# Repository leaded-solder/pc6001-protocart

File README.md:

# PC-6001 Pico Cartridge
Raspberry Pi Pico based cartridge

# Version History
## v1.2
Refined version of v1.1
 - Add pull-up to data buffer IN/out to make sure it works properly during startup (paranoid)
 - Make address lines always IN using a +3.3v pull-up
 - Bypass caps for 74lvc245 to improve performance (paranoid)
 - Z80 WAIT pin wired to GPIO 27

## v1.1 (released)
Adds buffers for address/data multiplexing purposes

## v1.0 (released)
Initial version, unbuffered

# Open source stuff used
 * [Pablo Oyarzo poka-yoke library](https://github.com/PabloOyarzo/poka-yoke_rxtx)

# Special Thanks
 * alank2 on the Vintage Computer Festival forum, for measuring his Canyon Climber cartridge
 * thweasel on the FujiNet discord for helping check my design

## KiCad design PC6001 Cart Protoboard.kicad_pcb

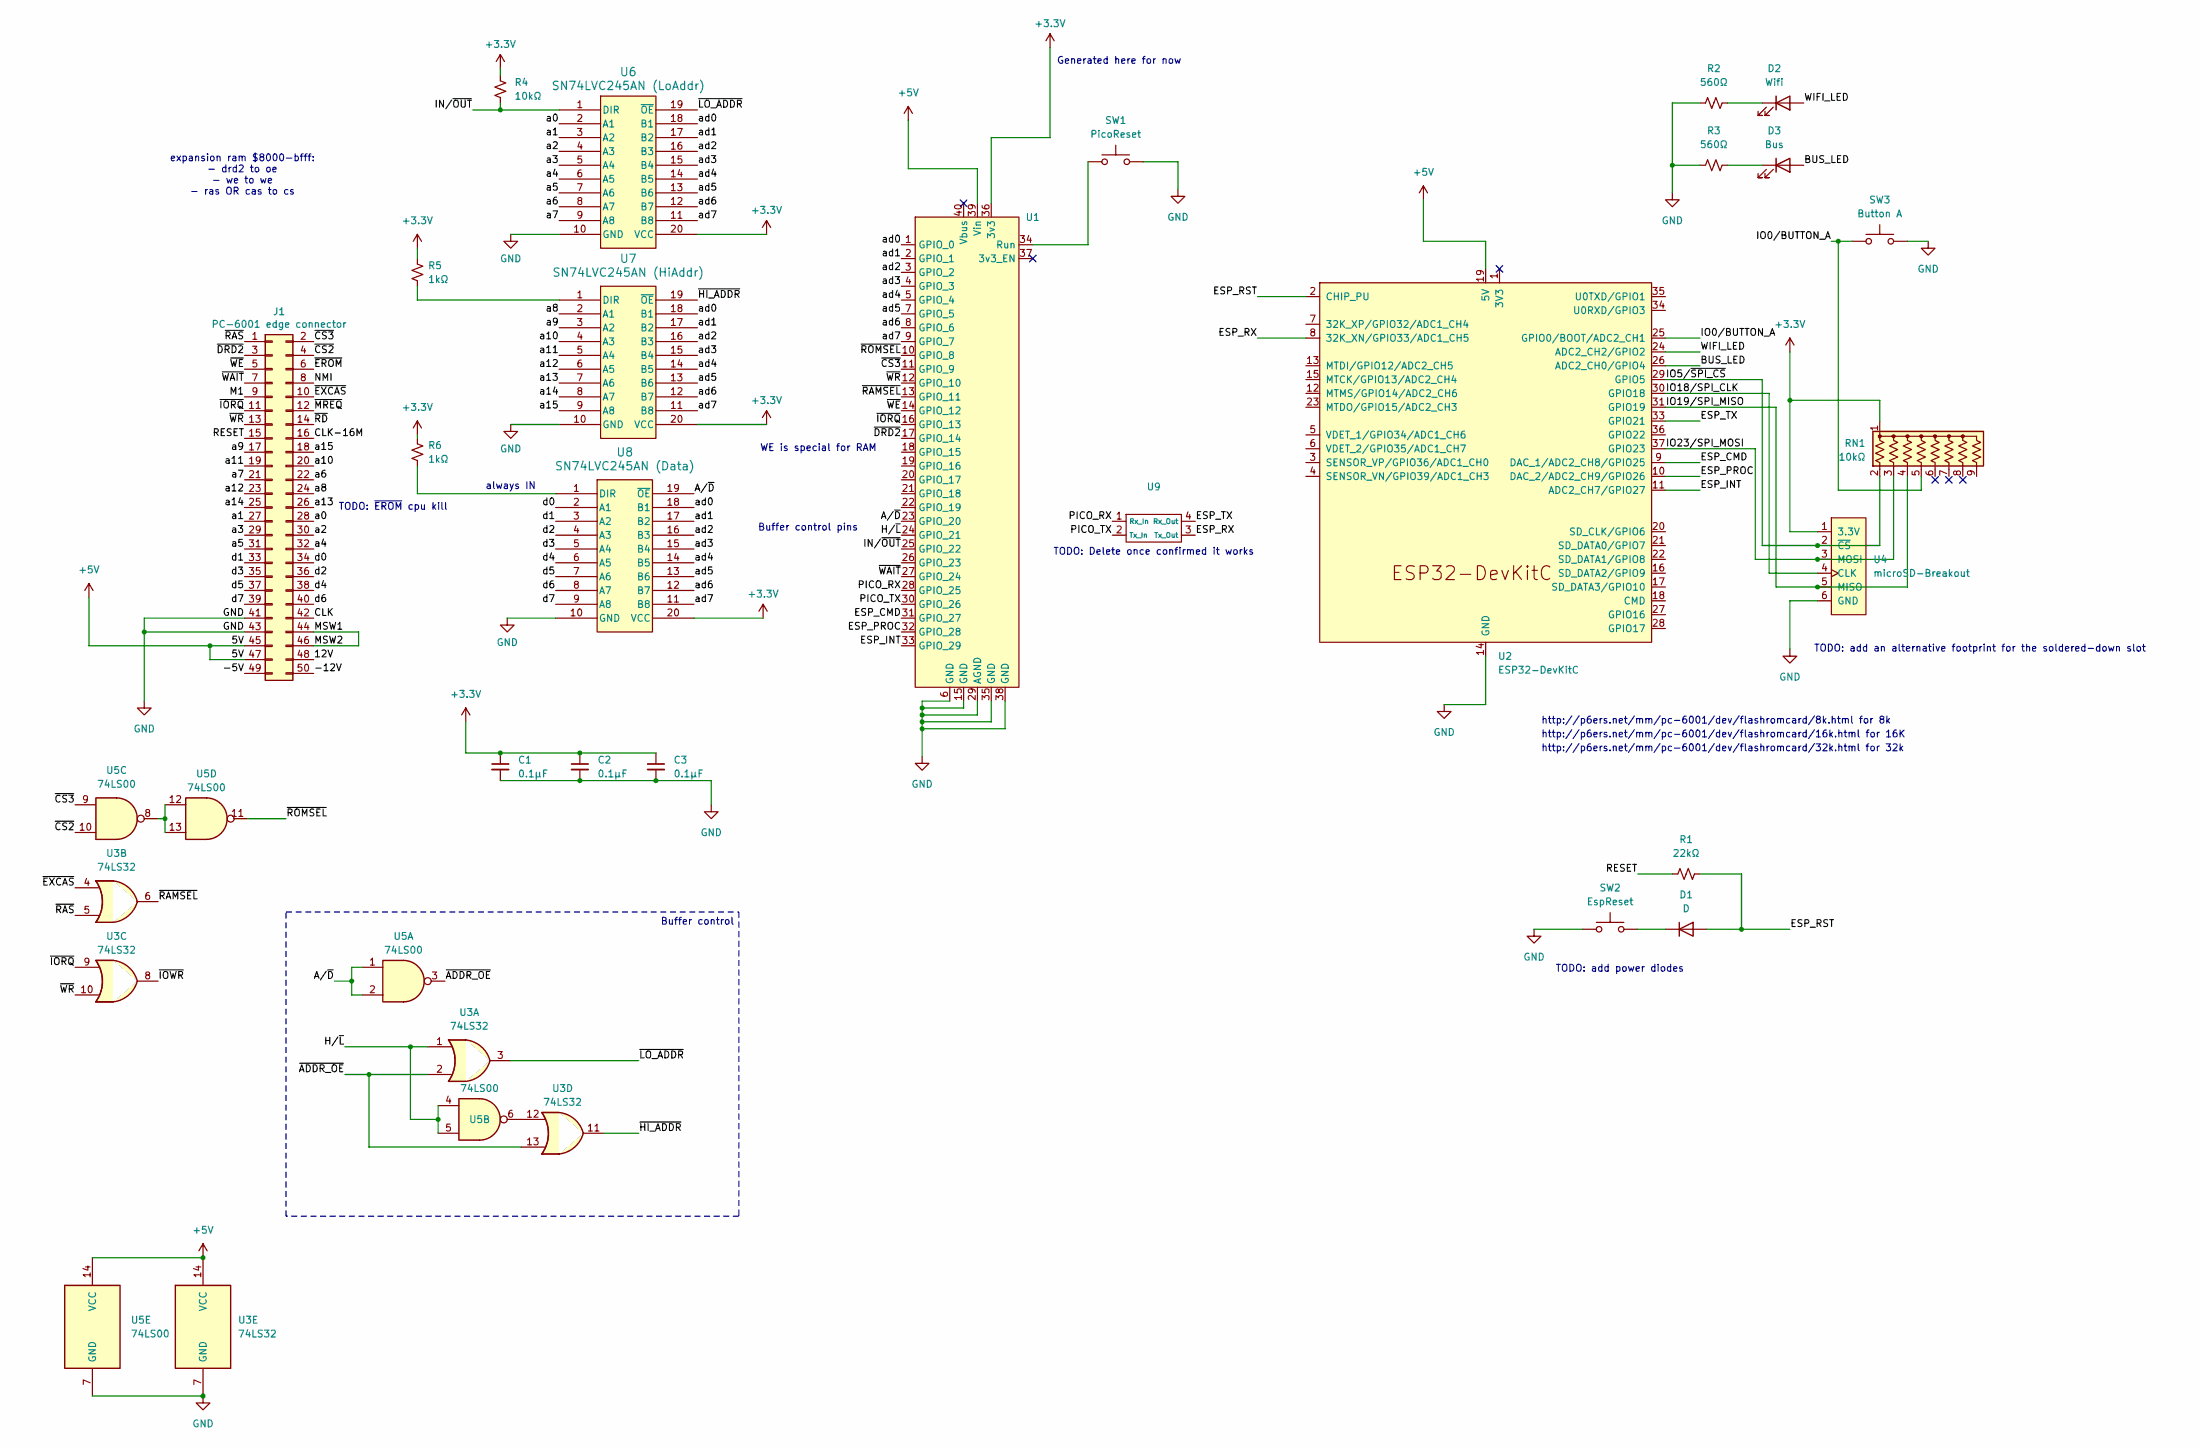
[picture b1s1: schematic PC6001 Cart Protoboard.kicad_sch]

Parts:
C1, C2, C3: 0.1µF; C_Disc_D5.0mm_W2.5mm_P2.50mm
D1: D; D_DO-35_SOD27_P7.62mm_Horizontal
D2: Wifi; LED_D3.0mm
D3: Bus; LED_D3.0mm
J1: PC-6001 edge connector; PC6001 Cartridge Connector
R1: 22kΩ; R_Axial_DIN0207_L6.3mm_D2.5mm_P10.16mm_Horizontal
R2, R3: 560Ω; R_Axial_DIN0207_L6.3mm_D2.5mm_P10.16mm_Horizontal
R4: 10kΩ; R_Axial_DIN0207_L6.3mm_D2.5mm_P10.16mm_Horizontal
R5, R6: 1kΩ; R_Axial_DIN0207_L6.3mm_D2.5mm_P10.16mm_Horizontal
RN1: 10kΩ; R_Array_SIP9
SW1: PicoReset; SW_PUSH_6mm
SW2: EspReset; SW_PUSH_6mm
SW3: Button A; SW_PUSH_6mm
U1: UltimatePico
U2: ESP32-DevKitC
U3: 74LS32
U4: microSD-Breakout; microSD_AliExpress
U5: 74LS00; DIP-14_W7.62mm_Socket_LongPads
U6: SN74LVC245AN (LoAddr); DIP-20_W7.62mm_Socket_LongPads
U7: SN74LVC245AN (HiAddr); DIP-20_W7.62mm_Socket_LongPads
U8: SN74LVC245AN (Data); DIP-20_W7.62mm_Socket_LongPads
U9: poka-yoke_rxtx

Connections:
+3.3V: C1.1, C2.1, C3.1, R4.1, R5.1, R6.1, RN1.1 (common), U1.36 (3v3), U4.1 (3.3V), U6.20 (VCC), U7.20 (VCC), U8.20 (VCC)
+5V: J1.45, J1.47, U1.39 (Vin), U2.19 (5V), U3.14 (VCC), U5.14 (VCC)
/12V: J1.48
/-5V: J1.49
/-12V: J1.50
/A/~D: U1.23 (GPIO_20), U5.1, U5.2, U8.19 (~OE)
/BUS_LED: D3.2 (A), U2.26 (ADC2_CH0/GPIO4)
/CLK: J1.42
/CLK-16M: J1.16
/ESP_CMD: U1.31 (GPIO_27), U2.9 (DAC_1/ADC2_CH8/GPIO25)
/ESP_INT: U1.33 (GPIO_29), U2.11 (ADC2_CH7/GPIO27)
/ESP_PROC: U1.32 (GPIO_28), U2.10 (DAC_2/ADC2_CH9/GPIO26)
/ESP_RST: D1.2 (A), R1.2, U2.2 (CHIP_PU)
/ESP_RX: U2.8 (32K_XN/GPIO33/ADC1_CH5), U9.3 (Tx_Out)
/ESP_TX: U2.33 (GPIO21), U9.4 (Rx_Out)
/H/~L: U1.24 (GPIO_21), U3.1, U5.4, U5.5
/IN/~OUT: R4.2, U1.25 (GPIO_22), U6.1 (DIR)
/IO0/BUTTON_A: RN1.5 (R4), SW3.1, U2.25 (GPIO0/BOOT/ADC2_CH1)
/IO5/~SPI_CS: RN1.2 (R1), U2.29 (GPIO5), U4.2 (~CS)
/IO18/SPI_CLK: U2.30 (GPIO18), U4.4 (CLK)
/IO19/SPI_MISO: RN1.4 (R3), U2.31 (GPIO19), U4.5 (MISO)
/IO23/SPI_MOSI: RN1.3 (R2), U2.37 (GPIO23), U4.3 (MOSI)
/M1: J1.9
/MSW1: J1.44, J1.46
/NMI: J1.8
/PICO_RX: U1.28 (GPIO_25), U9.1 (Rx_In)
/PICO_TX: U1.30 (GPIO_26), U9.2 (Tx_In)
/RESET: J1.15, R1.1
/WIFI_LED: D2.2 (A), U2.24 (ADC2_CH2/GPIO2)
/a0: J1.28, U6.2 (A1)
/a1: J1.27, U6.3 (A2)
/a2: J1.30, U6.4 (A3)
/a3: J1.29, U6.5 (A4)
/a4: J1.32, U6.6 (A5)
/a5: J1.31, U6.7 (A6)
/a6: J1.22, U6.8 (A7)
/a7: J1.21, U6.9 (A8)
/a8: J1.24, U7.2 (A1)
/a9: J1.17, U7.3 (A2)
/a10: J1.20, U7.4 (A3)
/a11: J1.19, U7.5 (A4)
/a12: J1.23, U7.6 (A5)
/a13: J1.26, U7.7 (A6)
/a14: J1.25, U7.8 (A7)
/a15: J1.18, U7.9 (A8)
/ad0: U1.1 (GPIO_0), U6.18 (B1), U7.18 (B1), U8.18 (B1)
/ad1: U1.2 (GPIO_1), U6.17 (B2), U7.17 (B2), U8.17 (B2)
/ad2: U1.3 (GPIO_2), U6.16 (B3), U7.16 (B3), U8.16 (B3)
/ad3: U1.4 (GPIO_3), U6.15 (B4), U7.15 (B4), U8.15 (B4)
/ad4: U1.5 (GPIO_4), U6.14 (B5), U7.14 (B5), U8.14 (B5)
/ad5: U1.7 (GPIO_5), U6.13 (B6), U7.13 (B6), U8.13 (B6)
/ad6: U1.8 (GPIO_6), U6.12 (B7), U7.12 (B7), U8.12 (B7)
/ad7: U1.9 (GPIO_7), U6.11 (B8), U7.11 (B8), U8.11 (B8)
/d0: J1.34, U8.2 (A1)
/d1: J1.33, U8.3 (A2)
/d2: J1.36, U8.4 (A3)
/d3: J1.35, U8.5 (A4)
/d4: J1.38, U8.6 (A5)
/d5: J1.37, U8.7 (A6)
/d6: J1.40, U8.8 (A7)
/d7: J1.39, U8.9 (A8)
/~ADDR_OE: U3.2, U3.13, U5.3
/~CS2: J1.4, U5.10
/~CS3: J1.2, U1.11 (GPIO_9), U5.9
/~DRD2: J1.3, U1.17 (GPIO_14)
/~EROM: J1.6
/~EXCAS: J1.10, U3.4
/~HI_ADDR: U3.11, U7.19 (~OE)
/~IORQ: J1.11, U1.16 (GPIO_13), U3.9
/~IOWR: U3.8
/~LO_ADDR: U3.3, U6.19 (~OE)
/~MREQ: J1.12
/~RAMSEL: U1.13 (GPIO_11), U3.6
/~RAS: J1.1, U3.5
/~RD: J1.14
/~ROMSEL: U1.10 (GPIO_8), U5.11
/~WAIT: J1.7, U1.27 (GPIO_24)
/~WE: J1.5, U1.14 (GPIO_12)
/~WR: J1.13, U1.12 (GPIO_10), U3.10
GND: C1.2, C2.2, C3.2, J1.41, J1.43, R2.1, R3.1, SW1.2, SW2.1, SW3.2, U1.6 (GND), U1.15 (GND), U1.29 (AGND), U1.35 (GND), U1.38 (GND), U2.14 (GND), U2.32 (GND), U2.38 (GND), U3.7 (GND), U4.6 (GND), U5.7 (GND), U6.10 (GND), U7.10 (GND), U8.10 (GND)
unnamed: D1.1 (K), SW2.2
unnamed: D2.1 (K), R2.2
unnamed: D3.1 (K), R3.2
unnamed: SW1.1, U1.34 (Run)
unnamed: U3.12, U5.6
unnamed: U5.8, U5.12, U5.13
unnamed: R5.2, U7.1 (DIR)
unnamed: R6.2, U8.1 (DIR)

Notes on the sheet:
http://p6ers.net/mm/pc-6001/dev/flashromcard/8k.html for 8k
http://p6ers.net/mm/pc-6001/dev/flashromcard/32k.html for 32k
TODO: ~{EROM} cpu kill
WE is special for RAM
Buffer control
TODO: Delete once confirmed it works
http://p6ers.net/mm/pc-6001/dev/flashromcard/16k.html for 16K
expansion ram $8000-bfff: - drd2 to oe - we to we - ras OR cas to cs
Generated here for now
TODO: add an alternative footprint for the soldered-down slot
always IN
Buffer control pins
TODO: add power diodes

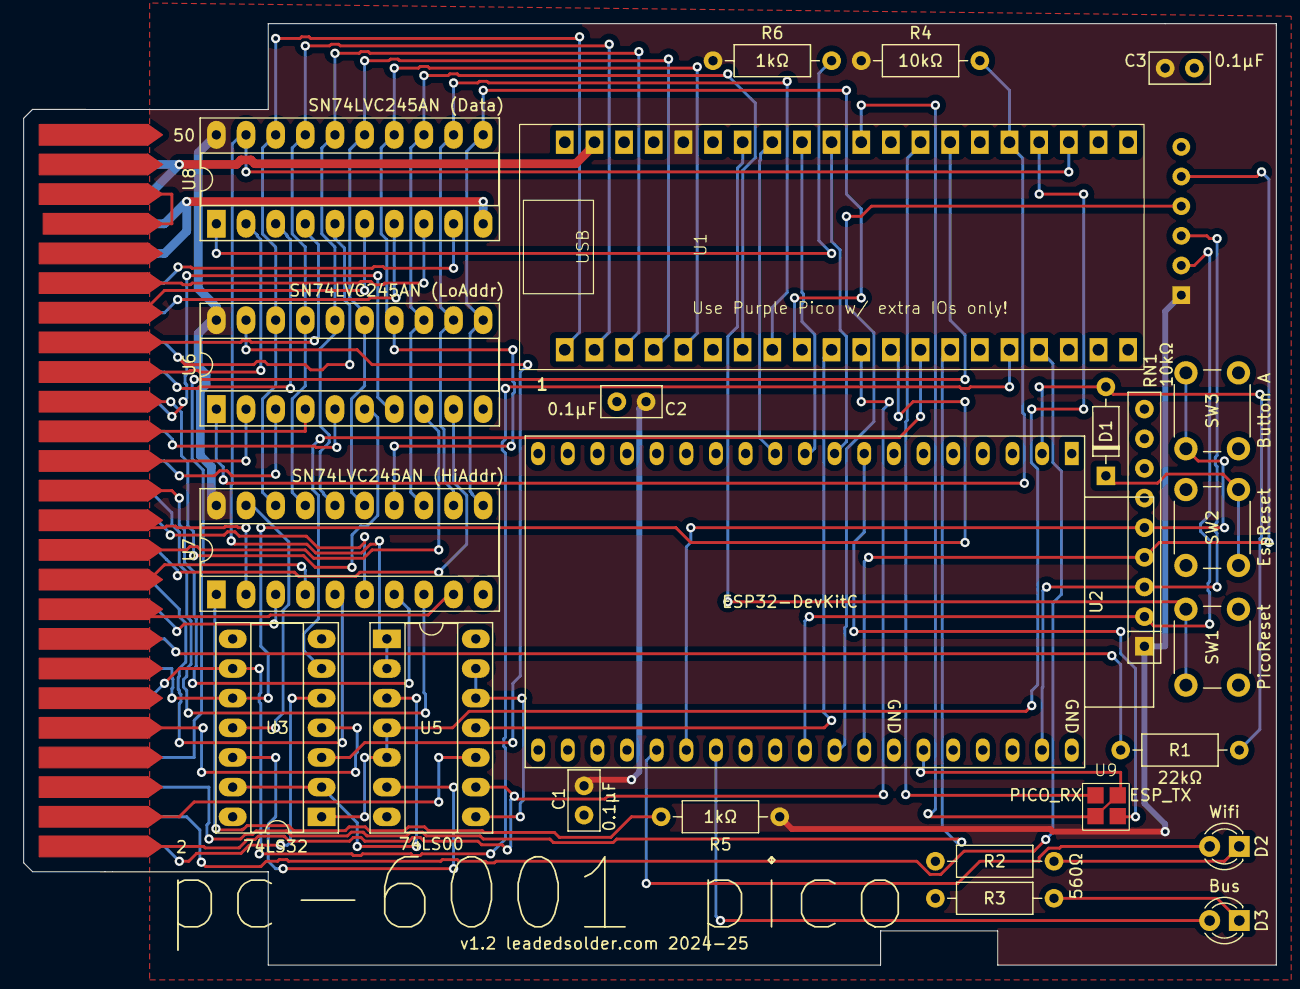
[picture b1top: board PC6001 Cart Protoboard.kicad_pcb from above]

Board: 4 copper layers, 107.3 x 80.6 mm, 26 parts (1 on the bottom side), 77 nets.

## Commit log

2019-11-27 Custom footprint
2019-11-27 Got an edge
2019-11-27 Get rid of 'pad bulge'
2019-11-27 Revise layout with new footprint
2019-11-27 10mm fingers
2019-11-27 25-pin power bus
2019-11-27 Probably have to re-think the power planes again
2019-11-27 Working my way through the pins now
2019-11-27 the board outline
2019-11-27 All pins routed, waiting for strips
2019-11-27 Strips added
2019-11-27 plot config
2019-11-27 v0.2 - 25 pin
2019-11-27 Shorty version
2019-11-27 Official measurements
2019-11-28 README
2019-11-28 PCB finger width increased to 1.77mm
2019-11-28 Edge width is now correct
2019-12-16 Fix it so the pads actually aren't masked
2019-12-23 Shortened pads to provide 1.25mm keepout
2022-02-06 v0.6
2022-02-06 Improve solder mask removal
2024-03-28 KiCad 7
2024-03-28 V1 released to jlcpcb
2024-03-29 Ignore lock files
2024-04-03 Very mild chamfer
2024-04-13 Bridge MSW
2024-04-15 Change to 16K design
2024-04-15 Badly-hacked ground pour but it passes DRC
2024-04-16 Submit v2 to fab
2024-05-12 Vertical-mount ZIFs should now clear system when inserted
2024-06-28 Shorten pin 44 to improve safety switch performance; KiCad 8
2024-07-24 Convincing top shell with no hardware or PCB holder
2024-07-24 Fix rib height inaccuracy
2024-07-24 TODO for romram
2024-07-24 Parameterize which half to draw
2024-07-24 Bottom is sort of roughed out
2024-07-24 Mating pins might work now?
2024-07-24 Looks right, but probably isn't
2024-07-24 Four in the roughly right place\?
2024-07-24 Make it a little longer
2024-07-24 Copy-paste strikes again
2024-07-24 Looking real good, but it still needs a clip
2024-07-24 UNTESTED STLs
2024-07-31 Clean up temp files
2024-08-12 Nice bottom chamfer.
2024-08-12 Shrink bottom half, pcb studs still seem wrong
2024-08-13 Trim out the ceiling to make more room for chips
2024-09-24 Extremely rough layout, footprint
2024-09-24 Power and ground
2024-09-24 Add keepout between teeth finally
2024-09-24 ESP32 added to board
2024-09-24 Z80 data, addr bus
2024-09-24 ESP32 connected
2024-10-09 ESP-reset button
2024-10-09 Something is wrong with the grid
2024-10-09 Stub out ram select
2024-10-09 TEMPORARILY putting SRAM in the ESP
2024-10-09 Added an AliExpress microSD card module
2024-10-09 Button A
2024-10-16 Export to v1
2024-10-28 Add entire a8picocart firmware
2024-10-28 Credits and caveats
2024-10-28 Ignore CMake build files
2024-10-28 Ignore uf2 build products
2024-10-28 About to generate rom
2024-10-28 Generate boot rom for header
2024-10-28 In theory, a ROM thing
2024-10-28 Mask re-reading
2024-10-28 rename output file
2024-10-28 Slowly hacking up all this code until it works
2024-10-29 Try an overclock
2024-10-29 Undo overclock
2024-10-29 Pointless cleanup
2024-10-29 Fix one obvious bug off the bat
2024-10-29 Include guards
2024-10-30 Time stamp the header
2024-10-30 oopsie on '08
2024-10-30 Rough out locs
2024-10-30 Make more room
2024-10-30 More stuff
2024-10-30 Add names to masks
2024-10-30 Stale comment cleanup
2024-11-09 Rebuilt tools, added more to ignore
2024-11-23 Make schematic larger to prepare for buffers
2024-11-23 Sketching out modified 74lvc245
2024-11-23 Wire in ramsel and wr so now we can be sram
2024-11-23 Add IORQ and CS3
2024-11-23 Move high address lines to 245
2024-11-23 Make things make more sense
2024-11-23 Random kicad diff
2024-11-23 RAM needs WE pin for some reason
2024-11-27 Buffers starting, RAMWR not right
2024-11-27 Convenience signals to use up some gates
2024-11-27 Buffer control pins
2024-11-27 Place nand gate
2024-11-27 more room for 245s
2024-11-27 Fully routed
2024-11-27 Source 3v3 from Pico for now
2024-11-27 ESP_INT restored
2024-11-27 Restore ESP_CMD, ESP_PROC
2024-11-27 No-connect the 10k
2024-11-27 Release version 1.1
2024-12-20 Frantically add caps
2024-12-21 Tie address buffer IN/out to always high
2024-12-21 Start tracking changes
2025-01-02 Trying to figure out the v2 board
2025-01-02 Pull-up instead of dead short for DIR
2025-01-02 Safety pull-ups routed
2025-01-02 Fixing unrouted errors
2025-01-02 Note to self for future
2025-01-02 Forcibly route WAIT to GPIO27
2025-01-02 WAIT pin arrives
2025-01-03 Get rid of stale comments
2025-01-03 Ultimate RP2040 is a little longer than we thought
2025-01-06 Exclusion
2025-01-07 Make 8K version first (Hello World) to make sure that still works
2025-01-07 CS3 logic
2025-01-07 Oops
2025-01-09 WORKING 8K - only CS2 checked
2025-01-09 CS3 not working
2025-01-09 Use 16k addresses
2025-01-09 CS3 is tied to a13 and should shift it up anyway
2025-01-10 16K LOAD!!!
2025-01-10 Create LICENSE
2025-01-15 Actually pop masks properly
2025-04-29 Improve headerize to mention source ROM
2025-04-29 Semi-intelligent padding to 8K, 16K
2025-04-29 Less stupid extend
2025-06-29 Make measurements clearer
2025-06-29 Trying to figure out case...
2025-06-30 TurboCase shenanigans
2025-07-02 More measurements
2025-10-15 Add poka-yoke for RX/TX
2025-10-15 Routed
